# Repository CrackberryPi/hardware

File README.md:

# Crackberry Pi hardware

## The plan

The idea is to develop a complete and usable handheld system based on the Raspberry Pi. For this purpose we plan to create a PCB that will provide a small touch screen, a tiny keyboard and some other features. Together with a custom enclosure and a Lithium Ion battery this would form a complete handheld system.

## Progress

####Up and running:

RTC -- [code](http://www.100randomtasks.com/raspberry-pi-rtc)

Random generator -- Lots of noise, lots of 1s and 0s

IR RX -- Using LIRC able to record IR

####Tested but does not work:

Screen -- some wiring issues

Touch controller -- does not show up in i2cdetect

IR TX

####Not yet tested

Keyboard controller

FM

Battery power and charging

EEPROM

## Hardware functionality

### Screen

3.5" 480x320 resistive touch screen. A number of parties sell boards to interface such screens to the Rasberry Pi already. The screens are generally more or less exactly the same size as the Raspberry Pi.

The preliminary candidate is the [CFAF320480C4-035T-TS](https://www.crystalfontz.com/product/CFAF320480C4035TTS#pcn).

The screen has an integrated Himax HX8357-B microcontroller. It is capable of handling DPI, MIPI and SPI interfaces. The latter we will use, connected directly to the RPi headers.

The resistive touchscreen requires an additional driver IC, for which we will use the [TSC2007](http://www.ti.com/lit/an/slaa364/slaa364.pdf), which runs on I2C leaving the entire SPI bus for the screen.

LED backlight can be dimmed using pulse width modulation.

The screen's reset pin is wired to GPIO6. This pin should be pulsed low after bootup and then be kept high for normal operation.

The chip select pin CE0 is wired to GPIO8.
```
Chip select input
Low:
 Controller chip is selected. Communications with host is possible.
High:
 Controller chip is not selected. Host interface signals are ignored by the controller.
```

### Keyboard

Looks like we'll go for the same technology (and designer :) ) as [TOHKBD](https://www.kickstarter.com/projects/2028347278/tohkbd-the-other-half-keyboard-for-your-jolla), with the difference that the Crackberry Pi's keyboard will be narrower. The following is a preliminary key layout:

```
         !     @     #     $     %     ^     &     *     (     )     Del
  ESC   1     2     3     4     5     6     7     8     9     0     BS

         F11   F12   {     }     [     ]     _     -     +     =
  TAB     Q     W     E     R     T     Y     U     I     O     P     CR

                                         ;     :     '     " 
  Caps      A     S     D     F     G     H     J     K     L     CR  CR

             ~     `                       <     >     ? ,   PgUp  Ins \
  Shift       Z     X     C     V     B     N     M     .     Up    /

                                                       Home  PgDn  End
  Sym   Ctrl  Alt              Spacebar                 Left  Down  Right
```

This keyboard is a combination of a metal frame, a silicon mat, plastic keys and a dome-sticker. Here's a picture:

The keyboard is controlled by the TCA8424

### Real Time Clock

Our circuit provide a Real Time Clock (RTC) to the Raspberry Pi. Plenty of ICs that do this. Will probably need its own miniature battery of some sort.

RTC ic: [MCP7940N](http://nl.mouser.com/Search/ProductDetail.aspx?R=MCP7940N-I%2fSNvirtualkeyMCP7940N-I%2fSNvirtualkey579-MCP7940N-I%2fSN)

Crystal: [CM200C](http://nl.mouser.com/ProductDetail/Citizen-Finetech-Miyota/CM200C-32768KDZB-UT/?qs=sGAEpiMZZMtzFpQ%252bfsc2VHRVaru4Cxjh)

Battery holder: [CR1216](http://nl.mouser.com/ProductDetail/Linx-Technologies/BAT-HLD-012-SMT/?qs=sGAEpiMZZMtbbFRYSpBbWwy2JjMrRsgr)

Header: [20x2 8.5mm](http://www.tme.eu/en/details/zl262-40dg/pin-headers/zl262-40dg#)

Display connector: [ZIF 50](http://www.digikey.com/product-detail/en/62684-501100ALF/609-1197-2-ND/1001511)

[RTC setup](http://tom.meinlschmidt.org/2014/02/19/mcp7940-rtc-with-pi/)

### Hardware random circuit

Serious cryptographic applications on embedded hardware invariably suffer from a lack of proper sources of random entropy. We're not simply trusting the Pi SoC chip for this, but we're providing an additional noise with two NPN transistors:

This needs to be powered by an 18V stepup circuit, powered by a NCP1406:

Quiescent current of circuit needs to investigated and if significant the Pi should be able to turn this on and off as random entropy will only be needed at boot time.

### Power, Lithium Ion Battery and charging circuit

Our system should optimally include a hardware on/off switch so that even security-conscious users can be certain the system is actually off when they think it is off.

This means adding an extra micro-usb port on our PCB, which is intended for charging the battery. The RPi will in turn be powered through the appropriate pin on the connector, with a switch in between. This allows the battery to charge while all other components are turned off.

Current best battery we can find is [this one](https://www.adafruit.com/products/354) from Adafruit, which fits rather perfectly and at 3.7V * 4.4 Ah would give us 16.28 Wh which at 5W gives us somewhat over 3 hrs of operation.

For the charging circuit we will use the BQ24297. This charging IC uses USB input power to charge the battery, has a step-up circuit supplying 5V@1.5A and a complete powerpath management for switching between battery usage and usb input with charging.

### FM transmitter

A [Si4713](http://nl.mouser.com/ProductDetail/Silicon-Labs/Si4713-B30-GM/?qs=sGAEpiMZZMvRDq0TKoyiQrUxOY0c9SY0) controlled over I2C steals the audio from the top of the 3.5jack. An antenna wire needs to be soldered on the PCB to transfer the signal.

### IR rx/tx

### HAT standard

[HAT](http://www.raspberrypi.org/introducing-raspberry-pi-hats/)s are Raspberry Pi expansion boards that conform to the [standard](https://github.com/raspberrypi/hats) set by the Raspberry Pi foundation. This involves a small I2C EEPROM filled with manufacturer information as well as size constraints (which we will not meet if we include a keyboard). We should nevertheless try to comply with this standard to the extent possible. This will also cause the Pi bootloader and standard software distributions to know about our GPIO pins, meaning less chance to break something.

This needs to be a CAT24C32 (32kbit, 4kbyte, same package and pin-out). By default the EEPROM is write-protected. By soldering the solder-jumper of shorting the testpads the write-protect is disabled. This will reduce the risk of accidental EEPROM resetting and breaking HAT-'compliance', but still give full freedom to the user.

Check [here](https://github.com/raspberrypi/hats/blob/master/eeprom-format.md) for further details on EEPROM programming.

### RPi GPIO usage

### Extended header

Additionally to the functionality inside, the possibility to still fiddle around will be kept intact by extending 18 pins on a [2x9 male header](http://nl.mouser.com/ProductDetail/Molex/87760-1816/?qs=sGAEpiMZZMs%252bGHln7q6pmzi5lyGzg2V24XJVwyxGDq0%3d) to the side. 

## License 

All development documentation, CAD drawings, driver source code that we develop ourselves is licensed under a <a rel="license" href="http://creativecommons.org/licenses/by-nc-sa/4.0/">Creative Commons Attribution-NonCommercial-ShareAlike 4.0 International License</a> unless specified otherwise. Please talk to us is you have commercial plans with any of this: we'll probably work something out.

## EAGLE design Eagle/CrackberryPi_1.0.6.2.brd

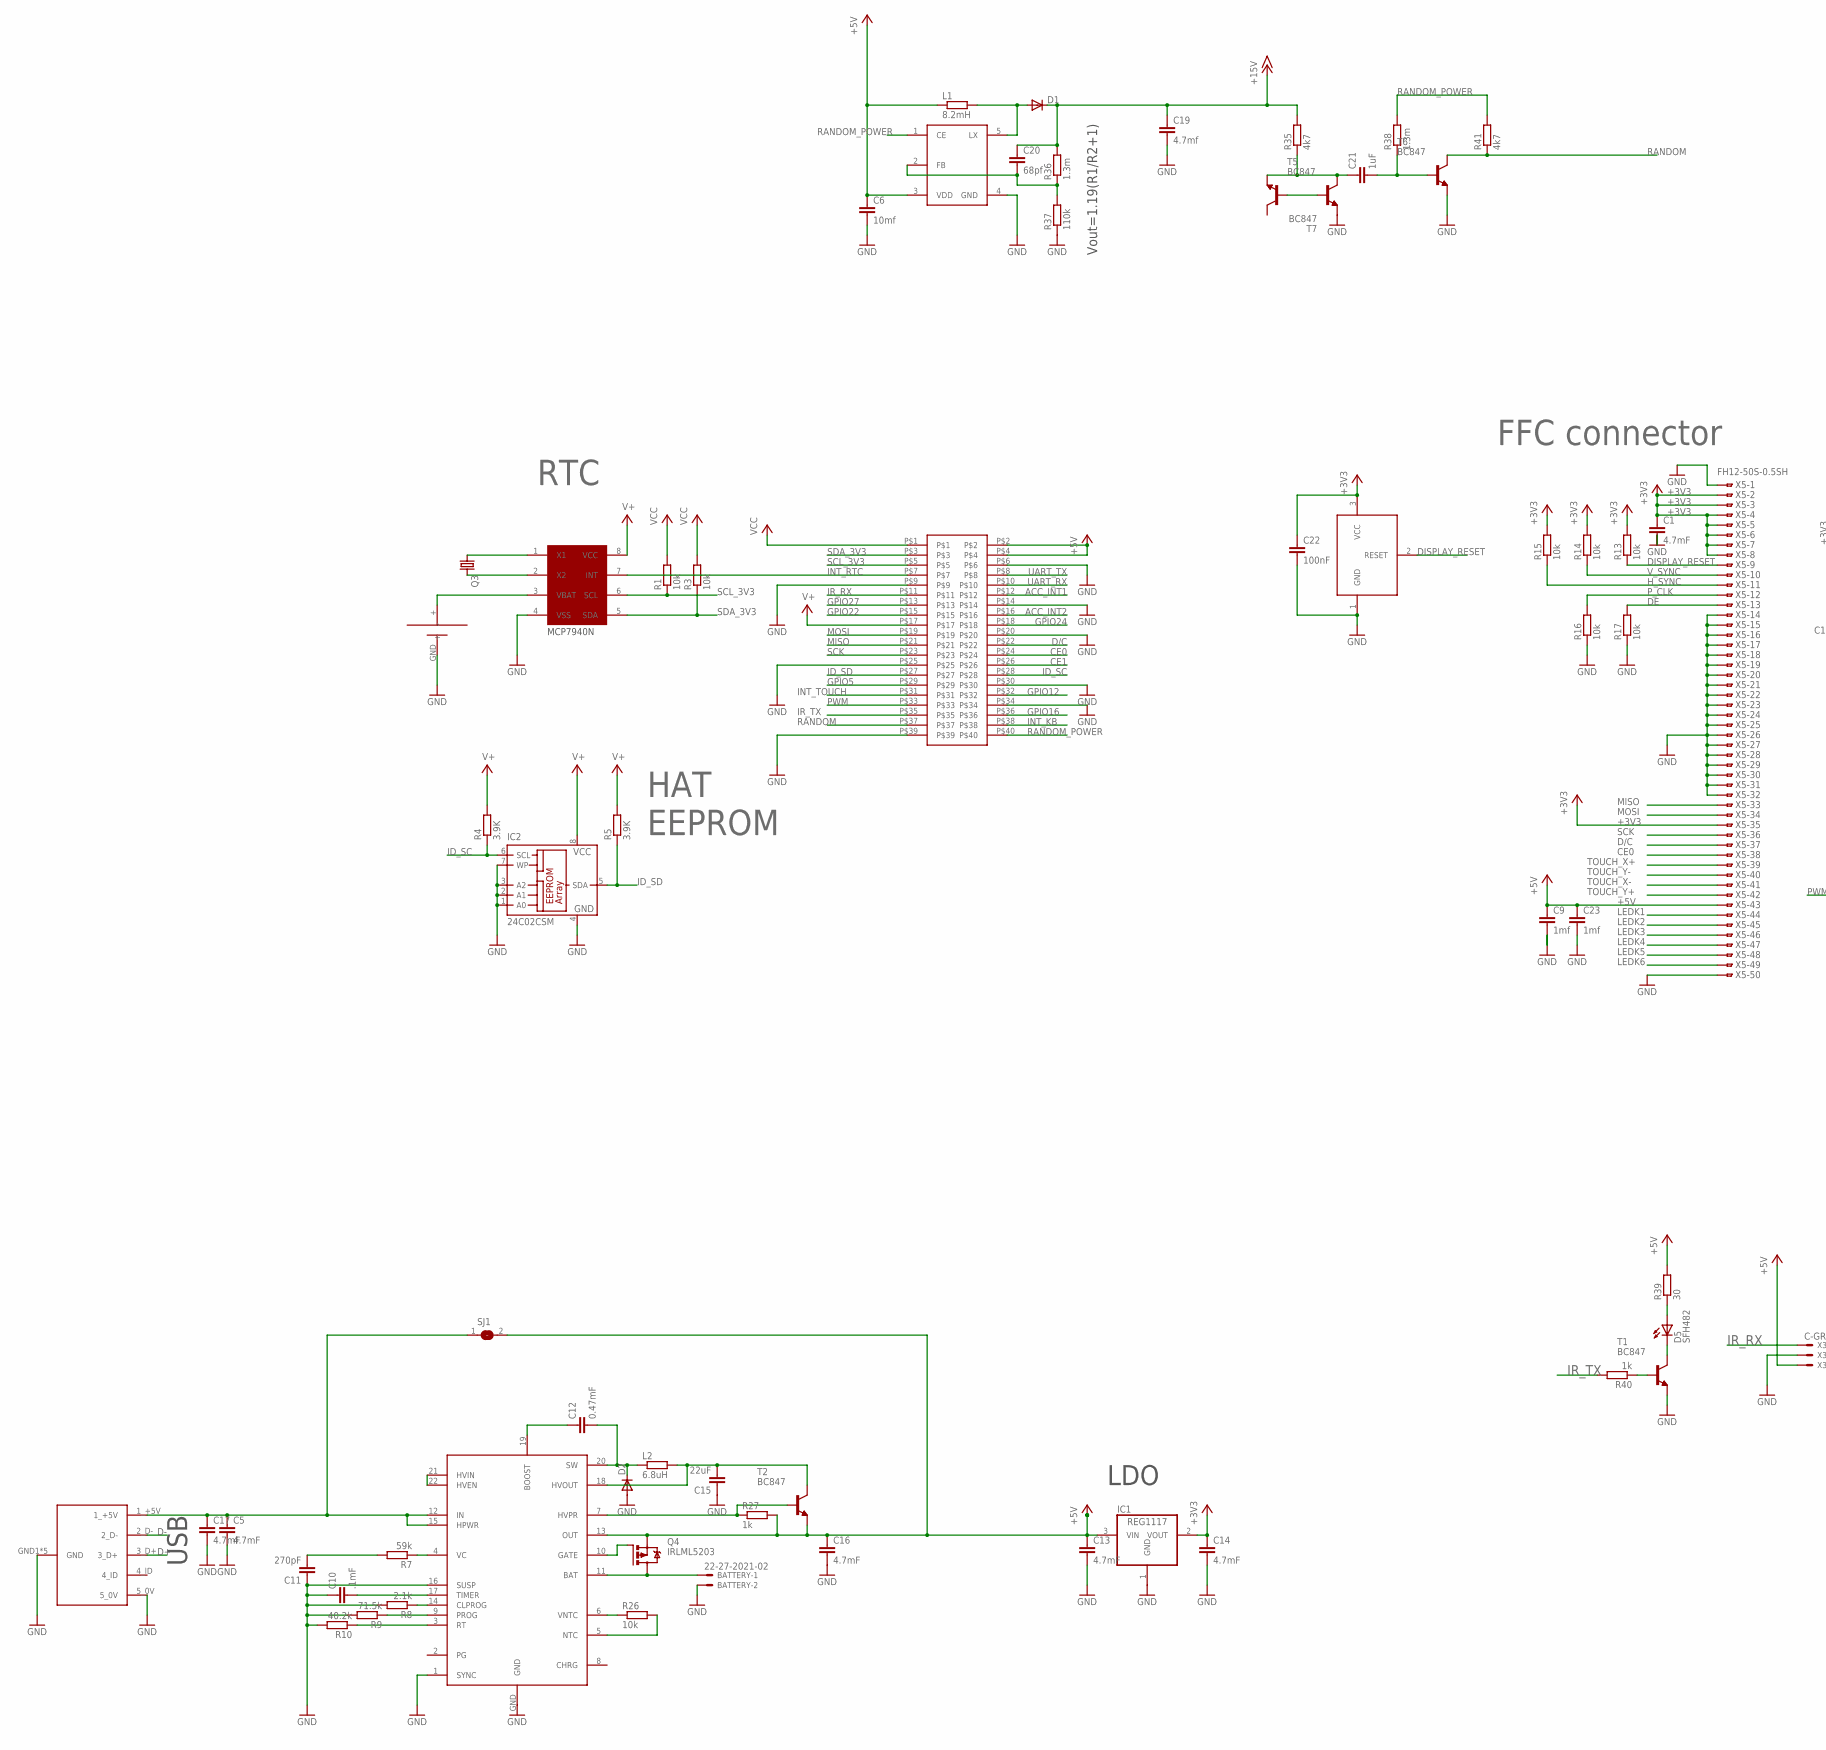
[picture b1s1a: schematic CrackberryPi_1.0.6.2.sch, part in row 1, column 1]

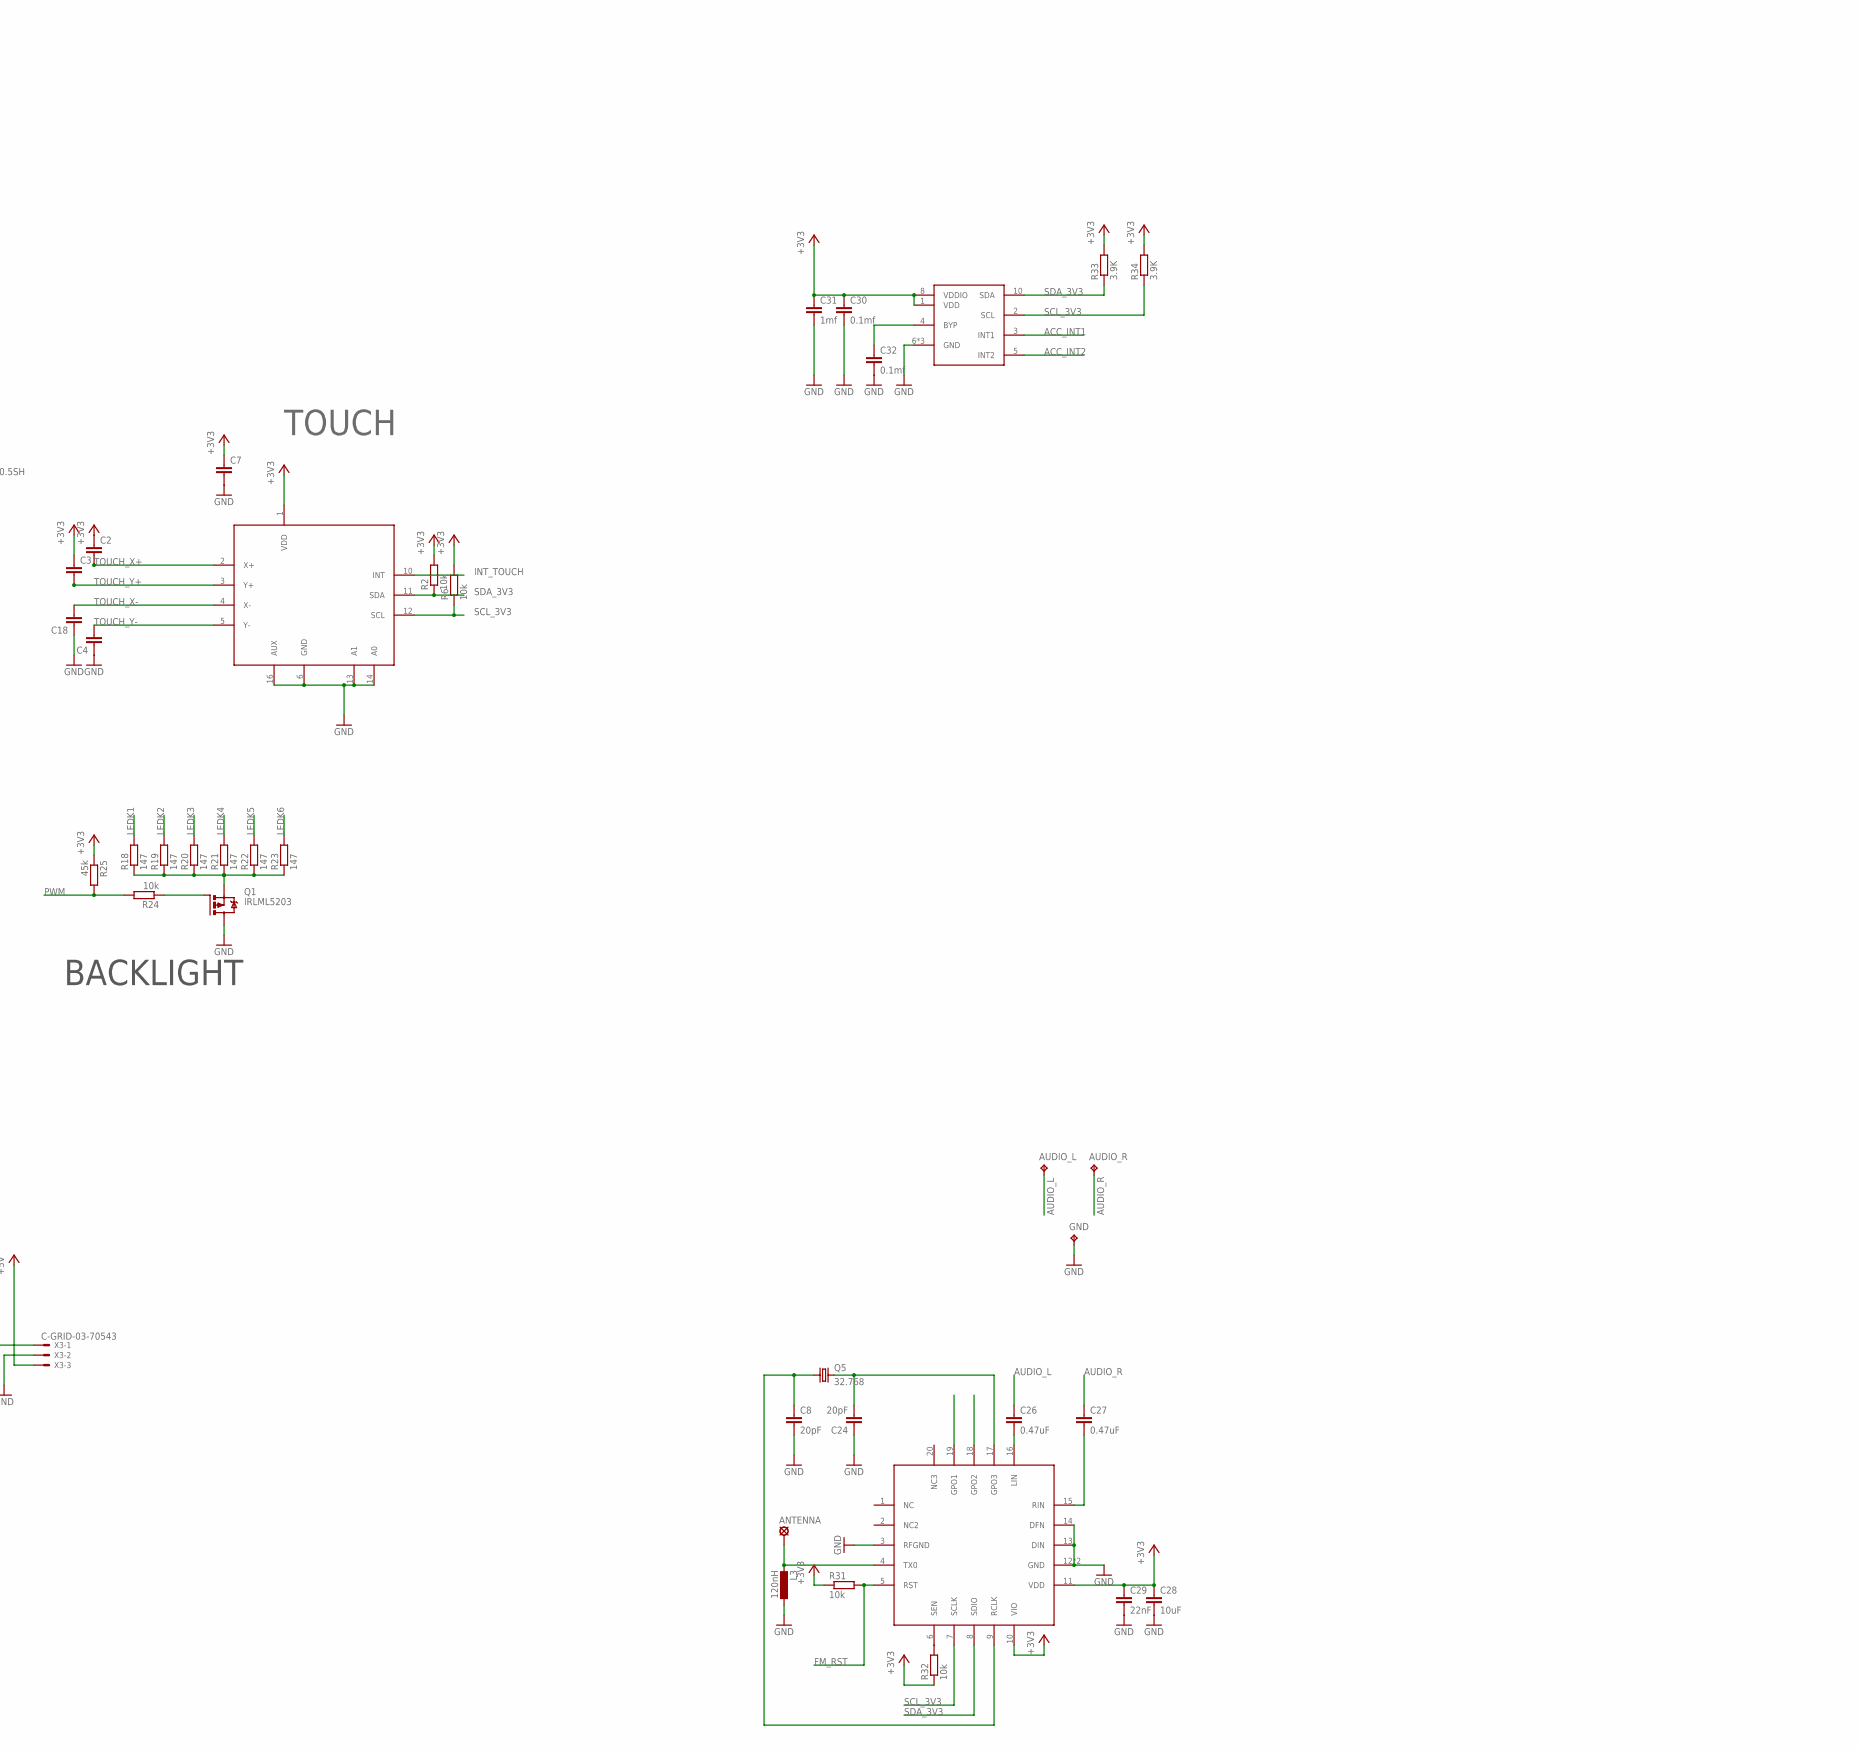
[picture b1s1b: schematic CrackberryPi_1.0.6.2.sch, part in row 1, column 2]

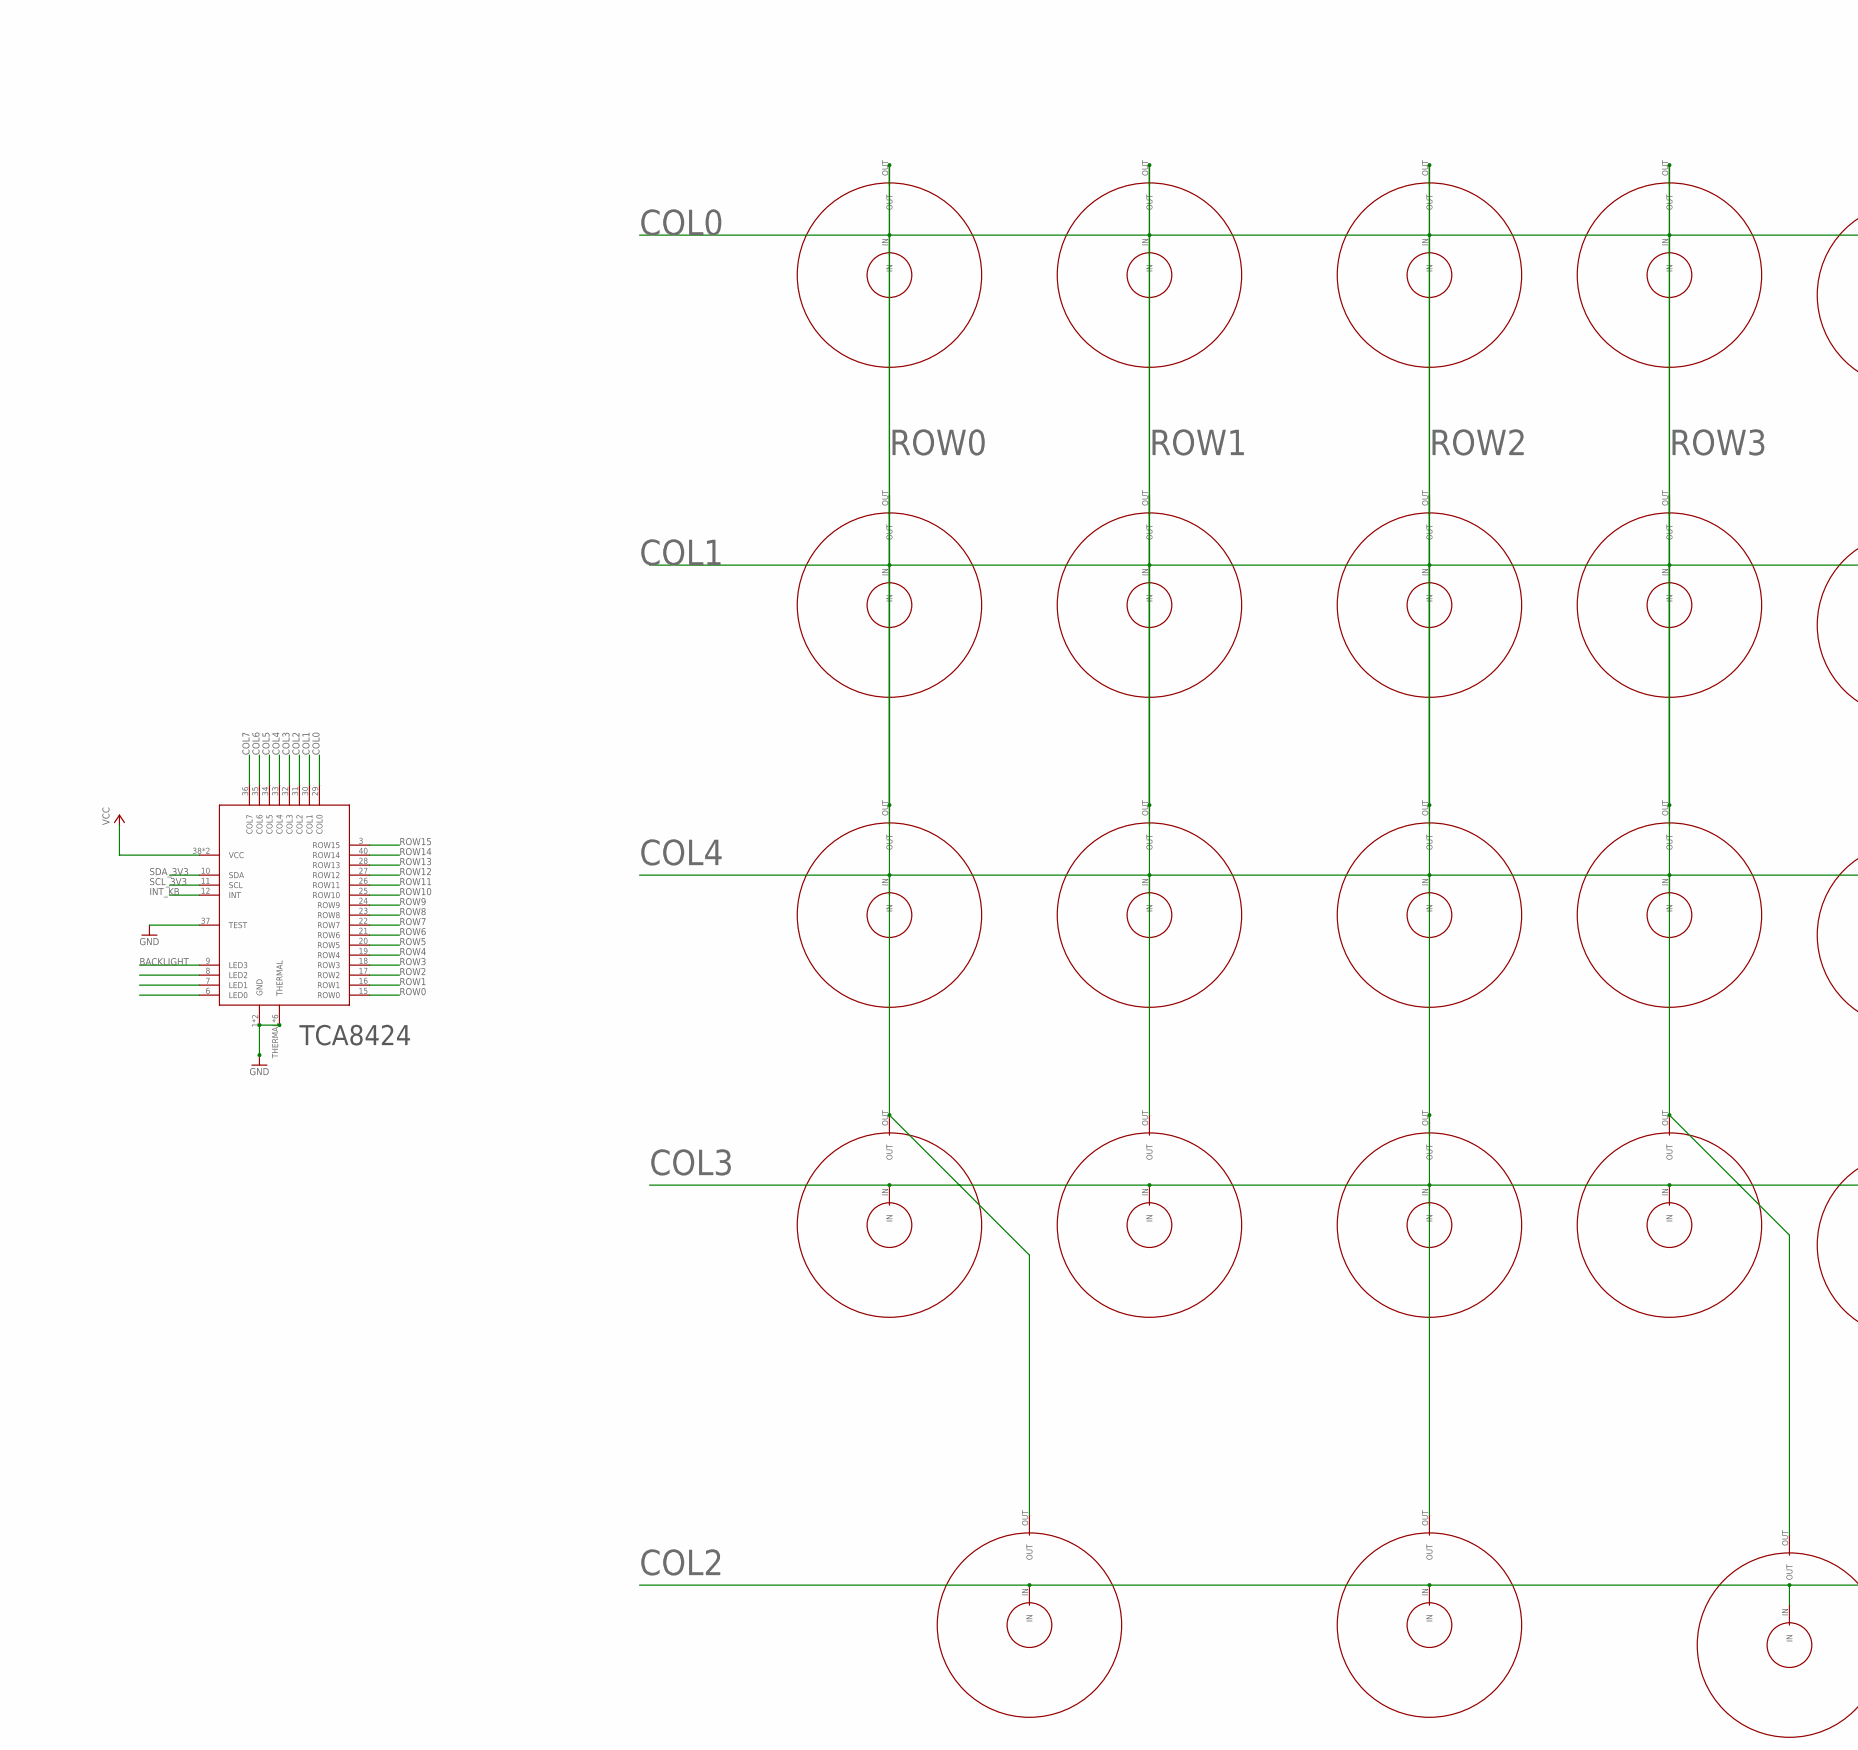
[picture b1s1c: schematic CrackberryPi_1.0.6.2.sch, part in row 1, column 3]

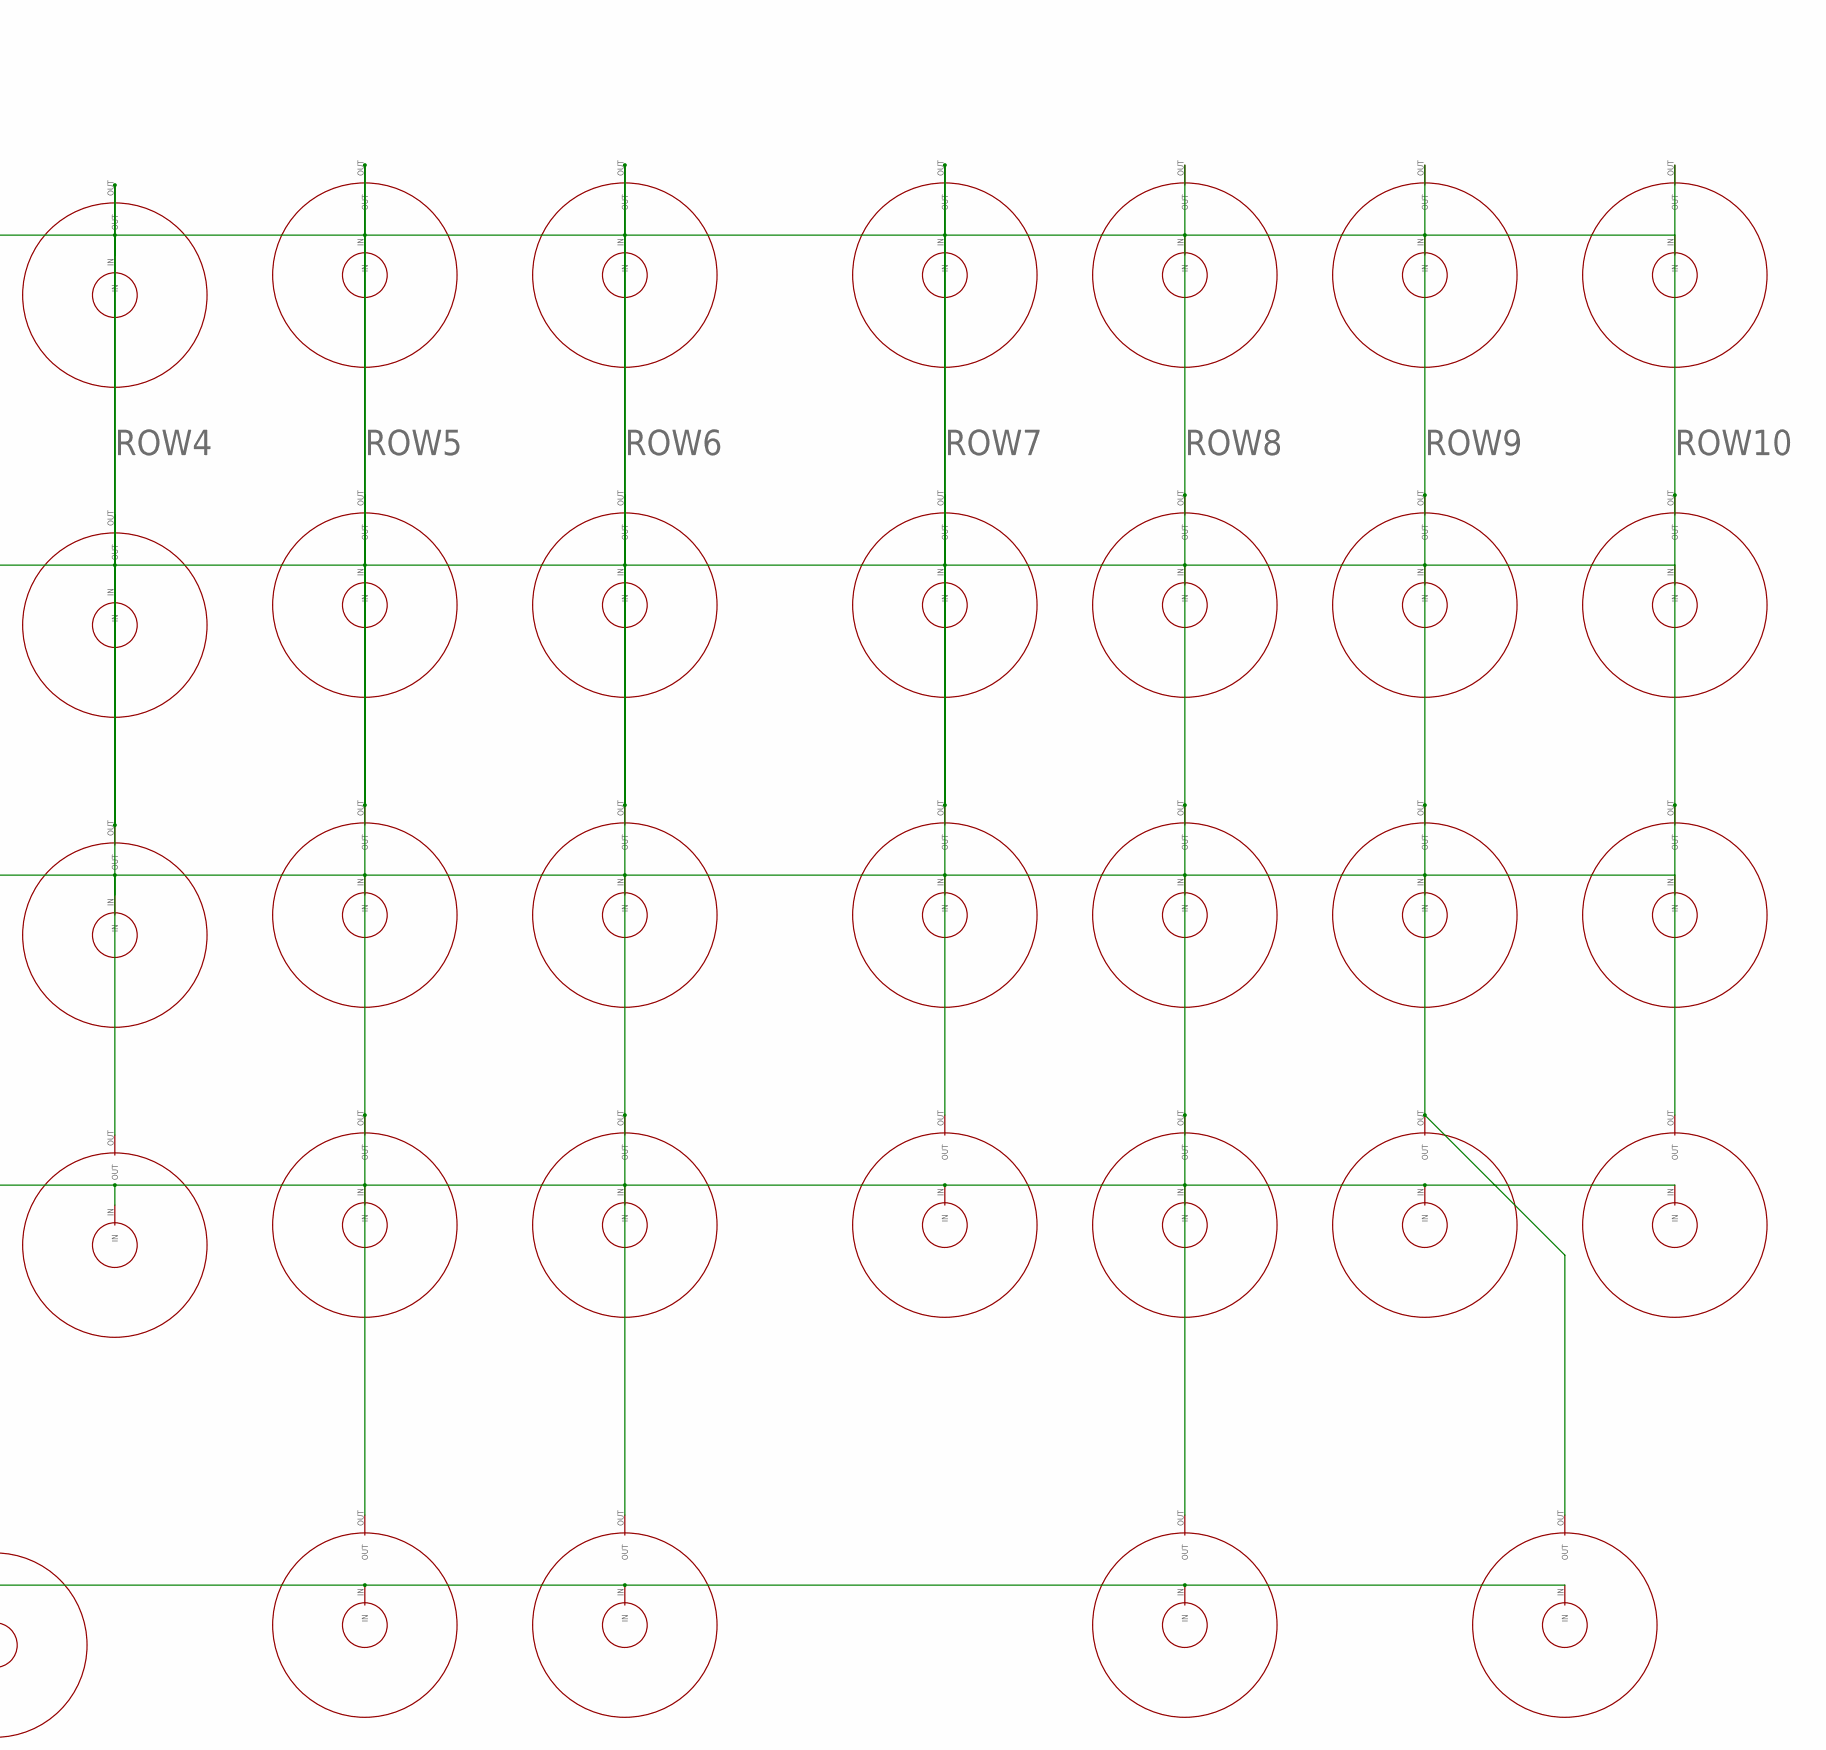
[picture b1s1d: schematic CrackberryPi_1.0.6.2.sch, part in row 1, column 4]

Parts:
1, 2, 3, 4, 5, 6, 7, 8, 9, 10, 11, 12, .: DOME; 4MM
!: DOME; 4MM
(: DOME; 4MM
): DOME; 4MM
,: DOME; 4MM
?: DOME; 4MM
@: DOME; 4MM
A: DOME; 4MM
ANTENNA: LSP10
AUDIO_L: TPB2,54; B2,54
AUDIO_R: TPB2,54; B2,54
B: DOME; 4MM
BATTERY: 22-27-2021-02; 6410-02
C: DOME; 4MM
C1, C5, C13, C14, C16, C17: 4.7mF; C0603
C2, C3, C4, C7, C18: C-EUC0603; C0603
C6: 10mf; C0603
C8, C24: 20pF; C0603
C9, C23, C31: 1mf; C0603
C10: .1mF; C0603
C11: 270pF; C0603
C12: 0.47mF; C0603
C15: 22uF; C1206
C19: 4.7mf; C0603
C20: 68pf; C0603
C21: 1uF; C0603
C22: 100nF; C0603
C26, C27: 0.47uF; C0603
C28: 10uF; C0603
C29: 22nF; C0603
C30, C32: 0.1mf; C0603
D: DOME; 4MM
D1, D2: DIODE-SOD123; SOD123
D5: SFH482
E: DOME; 4MM
F: DOME; 4MM
FN-RIGHT: DOME; 4MM
G: DOME; 4MM
GND: TPB2,54; B2,54
H: DOME; 4MM
I: DOME; 4MM
IC1: REG1117; SOT223
IC2: 24C02CSM; SO-08M
J: DOME; 4MM
K: DOME; 4MM
L: DOME; 4MM
L1: 8.2mH; R0805
L2: 6.8uH; R2010
L3: 120nH; L2012C
M: DOME; 4MM
N: DOME; 4MM
O: DOME; 4MM
P: DOME; 4MM
Q: DOME; 4MM
Q1, Q4: IRLML5203; MICRO3
Q3: CRYSTALMM20SS; MM20SS
Q5: 32.768; MM20SS
R: DOME; 4MM
R1, R2, R3, R6, R13, R14, R15, R16, R17, R24, R26, R31, R32: 10k; R0603
R4, R5, R33, R34: 3.9K; R0603
R7: 59k; R0603
R8: 2.1k; R0603
R9: 71.5k; R0603
R10: 40.2k; R0603
R18, R19, R20, R21, R22, R23: 147; R0603
R25: 45k; R0603
R27, R40: 1k; R0603
R35, R41: 4k7; R0603
R36, R38: 1.3m; R0603
R37: 110k; R0603
R39: 30; R0603
S: DOME; 4MM
SHIFT-RIGHT: DOME; 4MM
SHILFT-LEFT: DOME; 4MM
SJ1: SJ
SPACE1, SPACE2, SPACE3: DOME; 4MM
T: DOME; 4MM
T1, T2, T5, T6, T7: BC847; SOT23
U: DOME; 4MM
U$1: LTC4090; DFN22
U$2: NCP1406; SOT23-5L
U$3: RESETMONITOR; SOT23
U$4: CR1216
U$5: MCP7940N; SO08
U$6: TSC2007; TSSOP16
U$7: TCA8424; QFN40
U$9: MICRO_USB
U$11: HEADER; 20X2
U$12: SI4713; QFN20-3X3
U$13: ACCELLEROMETER; DFN-10_2X2
V: DOME; 4MM
W: DOME; 4MM
X: DOME; 4MM
X3: C-GRID-03-70543; 70543-03
X5: FH12-50S-0.5SH
Y: DOME; 4MM
Z: DOME; 4MM

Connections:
+3V3: C1.1, C2.1, C3.1, C7.1, C14.1, C22.1, C28.1, C29.1, C30.1, C31.1, IC1.2 (VOUT), R2.2, R6.2, R13.2, R14.2, R15.2, R25.1, R31.1, R32.1, R33.2, R34.2, U$3.3 (VCC), U$6.1 (VDD), U$12.10 (VIO), U$12.11 (VDD), U$13.1 (VDD), U$13.8 (VDDIO), X5.2, X5.3, X5.4, X5.5, X5.6, X5.7, X5.8, X5.35
+5V: C6.1, C9.1, C13.1, C16.1, C23.1, IC1.3 (VIN), L1.1, Q4.2 (S), R27.2, R39.2, SJ1.2, T2.2 (E), U$1.13 (OUT), U$2.3 (VDD), U$11.P$2, U$11.P$4, X3.3, X5.43
+15V: C19.1, C20.1, D1.C, R35.2, R36.2
ACC_INT1: U$11.P$12, U$13.3 (INT1)
ACC_INT2: U$11.P$16, U$13.5 (INT2)
AUDIO_L: AUDIO_L.TP, C26.1
AUDIO_R: AUDIO_R.TP, C27.1
BACKLIGHT: U$7.9 (LED3)
BASE: R40.1, T1.1 (B)
BAT: BATTERY.1, Q4.3 (D), U$1.11 (BAT)
BOOST: C12.1, U$1.19 (BOOST)
CE0: U$11.P$24, X5.38
CE1: U$11.P$26
COL0: 1.IN, 2.IN, 3.IN, 4.IN, 5.IN, 6.IN, 7.IN, 8.IN, 9.IN, 10.IN, 11.IN, U$7.29 (COL0)
COL1: 12.IN, E.IN, I.IN, O.IN, P.IN, Q.IN, R.IN, T.IN, U.IN, U$7.30 (COL1), W.IN, Y.IN
COL2: @.IN, FN-RIGHT.IN, SHIFT-RIGHT.IN, SHILFT-LEFT.IN, SPACE1.IN, SPACE2.IN, SPACE3.IN, U$7.31 (COL2)
COL3: !.IN, ,.IN, ..IN, ?.IN, B.IN, C.IN, M.IN, N.IN, U$7.32 (COL3), V.IN, X.IN, Z.IN
COL4: (.IN, ).IN, A.IN, D.IN, F.IN, G.IN, H.IN, J.IN, K.IN, L.IN, S.IN, U$7.33 (COL4)
COL5: U$7.34 (COL5)
COL6: U$7.35 (COL6)
COL7: U$7.36 (COL7)
COLLECTOR: D5.K (C), T1.3 (C)
D+: U$9.3_D+
D-: U$9.2_D-
D/C: U$11.P$22, X5.37
DE: R17.2, X5.13
DISPLAY_RESET: R13.1, U$3.2 (RESET), X5.9
FB: C20.2, R36.1, R37.2, U$2.2 (FB)
FM_RST: R31.2, U$12.5 (RST)
GND: BATTERY.2, C1.2, C4.1, C5.2, C6.2, C7.2, C8.2, C9.2, C10.1, C11.1, C13.2, C14.2, C15.1, C16.2, C17.2, C18.1, C19.2, C22.2, C23.2, C24.1, C28.2, C29.2, C30.2, C31.2, C32.2, D2.A, GND.TP, IC1.1 (GND), IC2.1 (A0), IC2.2 (A1), IC2.3 (A2), IC2.4 (GND), IC2.7 (WP), L3.1, Q1.3 (D), R8.2, R9.2, R10.2, R16.1, R17.1, R37.1, T1.2 (E), T5.2 (E), T6.2 (E), U$1.1 (SYNC), U$1.16 (SUSP), U$1.GND, U$2.4 (GND), U$3.1 (GND), U$4.GND (-), U$5.4 (VSS), U$6.6 (GND), U$6.13 (A1), U$6.14 (A0), U$6.16 (AUX), U$7.1 (GND), U$7.4 (GND), U$7.37 (TEST), U$7.THERMAL, U$7.VIA1 (THERMAL), U$7.VIA2 (THERMAL), U$7.VIA3 (THERMAL), U$7.VIA4 (THERMAL), U$7.VIA5 (THERMAL), U$9.5_0V, U$9.GND1 (GND), U$9.GND2 (GND), U$9.GND5 (GND), U$9.P$1 (GND), U$9.P$7 (GND), U$11.P$6, U$11.P$9, U$11.P$14, U$11.P$20, U$11.P$25, U$11.P$30, U$11.P$34, U$11.P$39, U$12.3 (RFGND), U$12.12 (GND), U$12.13 (DIN), U$12.14 (DFN), U$12.P$1 (GND), U$13.6 (GND), U$13.7 (GND), U$13.9 (GND), X3.2, X5.1, X5.14, X5.15, X5.16, X5.17, X5.18, X5.19, X5.20, X5.21, X5.22, X5.23, X5.24, X5.25, X5.26, X5.27, X5.28, X5.29, X5.30, X5.31, X5.32, X5.50
GPIO5: U$11.P$29
GPIO12: U$11.P$32
GPIO16: U$11.P$36
GPIO22: U$11.P$15
GPIO24: U$11.P$18
GPIO27: U$11.P$13
GPO1: U$12.19 (GPO1)
GPO2: U$12.18 (GPO2)
HVOUT: C15.2, L2.2, T2.3 (C), U$1.18 (HVOUT)
HVPR: R27.1, T2.1 (B), U$1.7 (HVPR)
H_SYNC: R15.1, X5.11
ID_SC: IC2.6 (SCL), R4.1, U$11.P$28
ID_SD: IC2.5 (SDA), R5.1, U$11.P$27
IN: C5.1, C17.1, SJ1.1, U$1.12 (IN), U$1.15 (HPWR), U$9.1_+5V
INT_KB: U$7.12 (INT), U$11.P$38
INT_RTC: U$5.7 (INT), U$11.P$7
INT_TOUCH: U$6.10 (INT), U$11.P$31
IR_RX: U$11.P$11, X3.1
IR_TX: R40.2, U$11.P$35
LEDK1: R18.2, X5.44
LEDK2: R19.2, X5.45
LEDK3: R20.2, X5.46
LEDK4: R21.2, X5.47
LEDK5: R22.2, X5.48
LEDK6: R23.2, X5.49
LX: D1.A, L1.2, U$2.5 (LX)
MISO: U$11.P$21, X5.33
MOSI: U$11.P$19, X5.34
unnamed: Q3.4 (2), U$5.2 (X2)
unnamed: Q3.1, U$5.1 (X1)
unnamed: R9.1, U$1.9 (PROG)
unnamed: R10.1, U$1.3 (RT)
unnamed: R8.1, U$1.14 (CLPROG)
unnamed: R7.1, U$1.4 (VC)
unnamed: C10.2, U$1.17 (TIMER)
unnamed: C11.2, R7.2
unnamed: U$1.21 (HVIN), U$1.22 (HVEN)
unnamed: Q1.2 (S), R18.1, R19.1, R20.1, R21.1, R22.1, R23.1
unnamed: C8.1, Q5.1, U$12.9 (RCLK)
unnamed: T5.1 (B), T7.1 (B)
unnamed: C24.2, Q5.4 (2), U$12.17 (GPO3)
unnamed: Q1.1 (G), R24.1
unnamed: R26.1, U$1.6 (VNTC)
unnamed: C26.2, U$12.16 (LIN)
unnamed: C27.2, U$12.15 (RIN)
unnamed: ANTENNA.MP, L3.2, U$12.4 (TX0)
unnamed: R26.2, U$1.5 (NTC)
unnamed: C21.1, R35.1, T5.3 (C), T7.2 (E)
unnamed: R32.2, U$12.6 (SEN)
unnamed: D5.A, R39.1
unnamed: C32.1, U$13.4 (BYP)
unnamed: C21.2, R38.1, T6.1 (B)
unnamed: Q4.1 (G), U$1.10 (GATE)
PWM: R24.2, R25.2, U$11.P$33
P_CLK: R16.2, X5.12
RANDOM: R41.1, T6.3 (C), U$11.P$37
RANDOM_POWER: R38.2, R41.2, U$2.1 (CE), U$11.P$40
ROW0: 1.OUT, A.OUT, Q.OUT, SHILFT-LEFT.OUT, U$7.15 (ROW0), Z.OUT
ROW1: 2.OUT, S.OUT, U$7.16 (ROW1), W.OUT, X.OUT
ROW2: 3.OUT, C.OUT, D.OUT, E.OUT, SPACE1.OUT, U$7.17 (ROW2)
ROW3: 4.OUT, F.OUT, R.OUT, SPACE2.OUT, U$7.18 (ROW3), V.OUT
ROW4: 5.OUT, B.OUT, G.OUT, T.OUT, U$7.19 (ROW4)
ROW5: 6.OUT, H.OUT, N.OUT, SPACE3.OUT, U$7.20 (ROW5), Y.OUT
ROW6: 7.OUT, J.OUT, M.OUT, SHIFT-RIGHT.OUT, U.OUT, U$7.21 (ROW6)
ROW7: 8.OUT, ?.OUT, I.OUT, K.OUT, U$7.22 (ROW7)
ROW8: 9.OUT, !.OUT, @.OUT, L.OUT, O.OUT, U$7.23 (ROW8)
ROW9: 10.OUT, (.OUT, ,.OUT, FN-RIGHT.OUT, P.OUT, U$7.24 (ROW9)
ROW10: 11.OUT, 12.OUT, ).OUT, ..OUT, U$7.25 (ROW10)
ROW11: U$7.26 (ROW11)
ROW12: U$7.27 (ROW12)
ROW13: U$7.28 (ROW13)
ROW14: U$7.40 (ROW14)
ROW15: U$7.3 (ROW15)
SCK: U$11.P$23, X5.36
SCL_3V3: R1.1, R6.1, R34.1, U$5.6 (SCL), U$6.12 (SCL), U$7.11 (SCL), U$11.P$5, U$12.7 (SCLK), U$13.2 (SCL)
SDA_3V3: R2.1, R3.1, R33.1, U$5.5 (SDA), U$6.11 (SDA), U$7.10 (SDA), U$11.P$3, U$12.8 (SDIO), U$13.10 (SDA)
SW: C12.2, D2.C, L2.1, U$1.20 (SW)
TOUCH_X+: C2.2, U$6.2 (X+), X5.39
TOUCH_X-: C18.2, U$6.4 (X-), X5.41
TOUCH_Y+: C3.2, U$6.3 (Y+), X5.42
TOUCH_Y-: C4.2, U$6.5 (Y-), X5.40
UART_RX: U$11.P$10
UART_TX: U$11.P$8
V+: IC2.8 (VCC), R4.2, R5.2, U$5.8 (VCC), U$11.P$17
VBAT+: U$4.+, U$5.3 (VBAT)
VCC: R1.2, R3.2, U$7.38 (VCC), U$7.39 (VCC), U$11.P$1
V_SYNC: R14.1, X5.10

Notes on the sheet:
RTC
HAT EEPROM
TOUCH
FFC connector
BACKLIGHT
MCP7940N
USB
LDO
Vout=1.19(R1/R2+1)
TCA8424

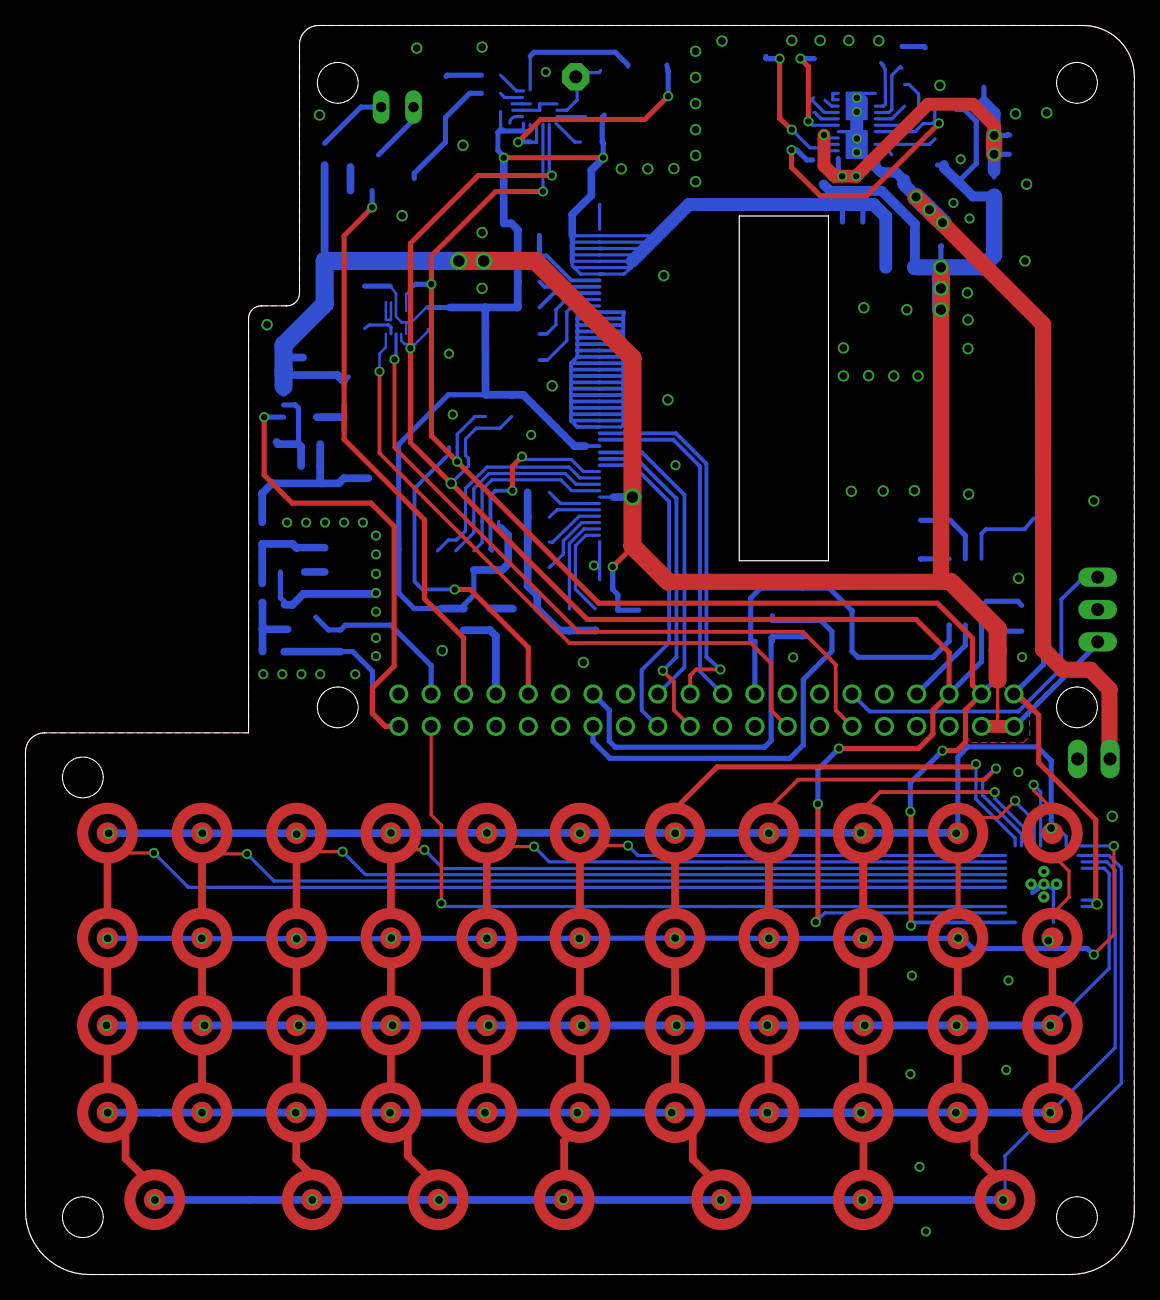
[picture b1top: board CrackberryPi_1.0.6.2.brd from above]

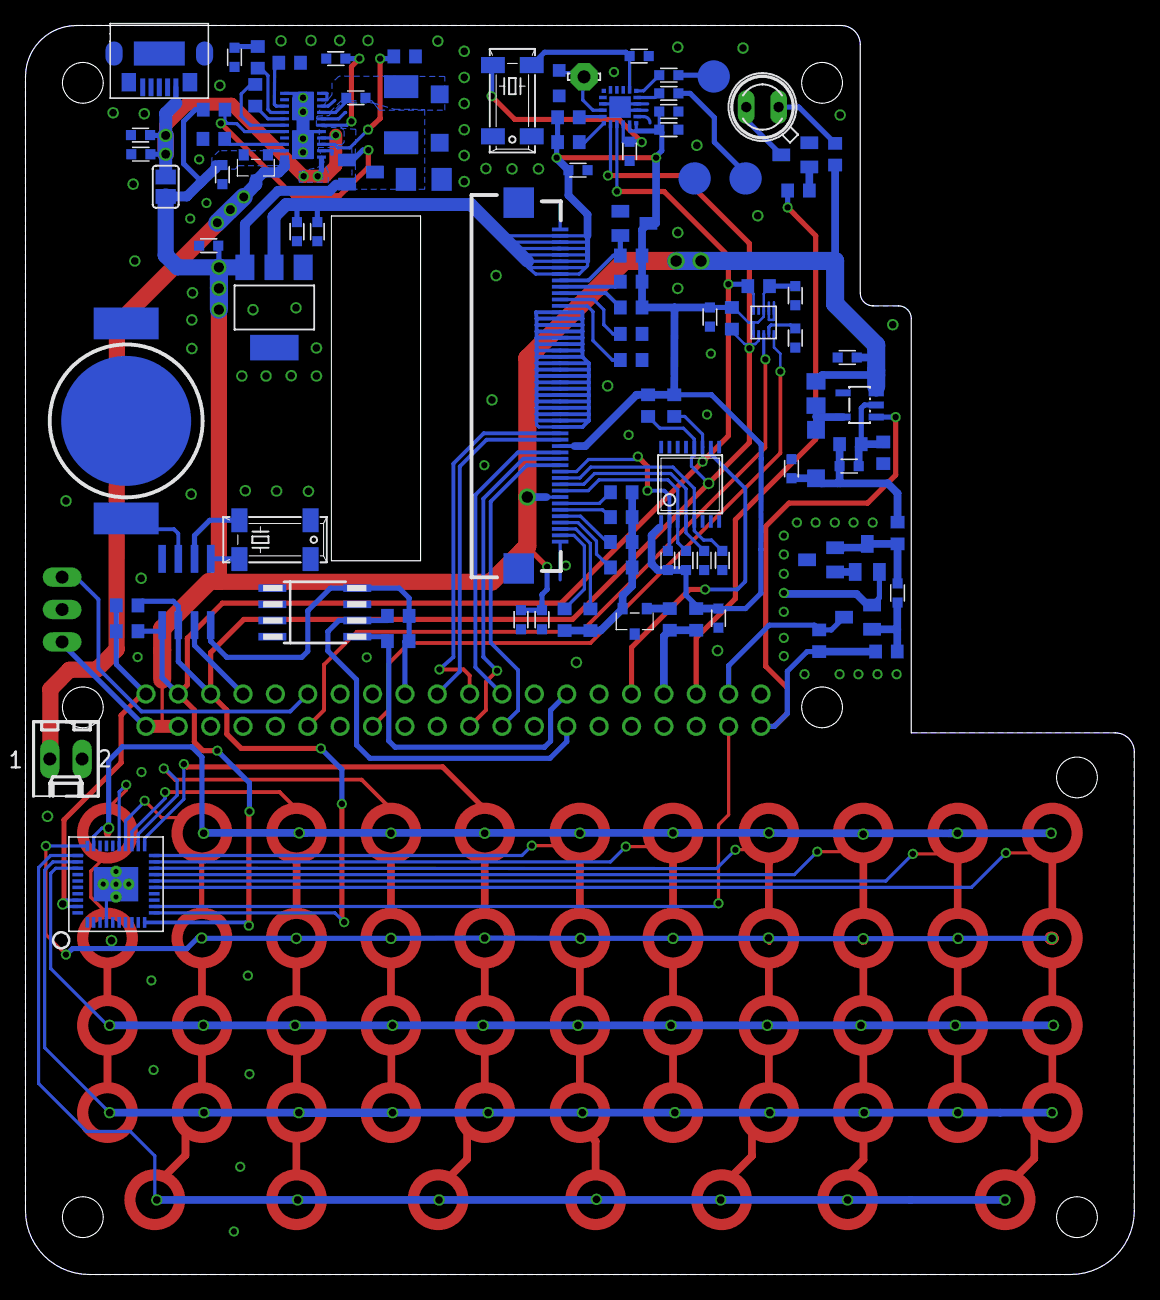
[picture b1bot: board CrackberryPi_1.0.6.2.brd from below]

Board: 2 copper layers, 87.0 x 98.0 mm, 154 parts (102 on the bottom side), 95 nets.
